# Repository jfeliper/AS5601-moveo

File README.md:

# AS5601-moveo
Placa con AS5601 y optoacopladores para adaptar a 24V
En un conector la salida de los optoacopladores de 24V
En otro conector el bus i2c para configurar el AS5601

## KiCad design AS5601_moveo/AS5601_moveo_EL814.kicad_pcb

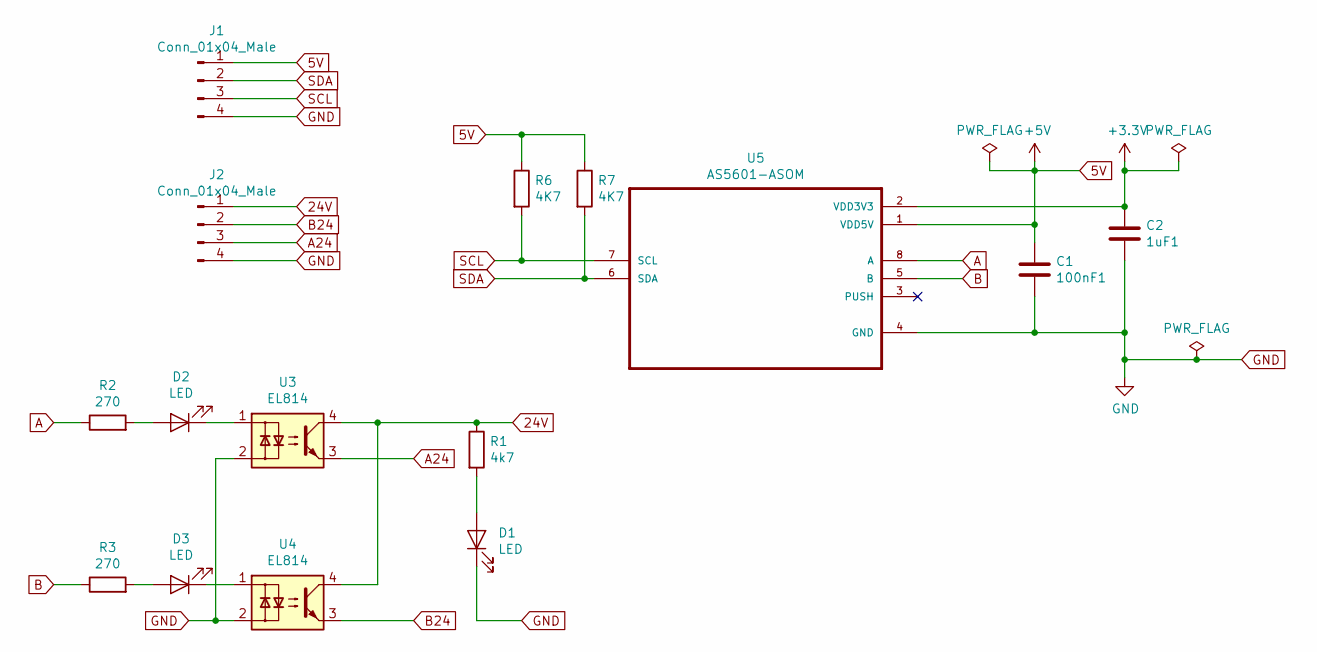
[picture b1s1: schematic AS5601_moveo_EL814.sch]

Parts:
C1: 100nF1; C_1206_3216Metric_Pad1.42x1.75mm_HandSolder
C2: 1uF1; C_1206_3216Metric_Pad1.42x1.75mm_HandSolder
D1, D2, D3: LED; LED_1206_3216Metric_Pad1.42x1.75mm_HandSolder
J1: Conn_01x04_Male; PinSocket_1x04_P2.54mm_Vertical
J2: Conn_01x04_Male; PinHeader_1x04_P2.54mm_Vertical
R1: 4k7; R_1206_3216Metric_Pad1.42x1.75mm_HandSolder
R2, R3: 270; R_1206_3216Metric_Pad1.42x1.75mm_HandSolder
R6, R7: 4K7; R_1206_3216Metric_Pad1.42x1.75mm_HandSolder
U3, U4: EL814; DIP-4_W7.62mm_SMDSocket_SmallPads
U5: AS5601-ASOM; SOIC-8_3.9x4.9mm_P1.27mm

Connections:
5V: C1.1, J1.1, R6.1, R7.1, U5.1 (VDD5V)
24V: J2.1, R1.1, U3.4, U4.4
+3V3: C2.1, U5.2 (VDD3V3)
A: R2.1, U5.8 (A)
A24: J2.3, U3.3
B: R3.1, U5.5 (B)
B24: J2.2, U4.3
GND: C1.2, C2.2, D1.1 (K), J1.4, J2.4, U3.2, U4.2, U5.4 (GND)
unnamed: D1.2 (A), R1.2
unnamed: D2.1 (K), U3.1
unnamed: D2.2 (A), R2.2
unnamed: D3.1 (K), U4.1
unnamed: D3.2 (A), R3.2
SCL: J1.3, R6.2, U5.7 (SCL)
SDA: J1.2, R7.2, U5.6 (SDA)

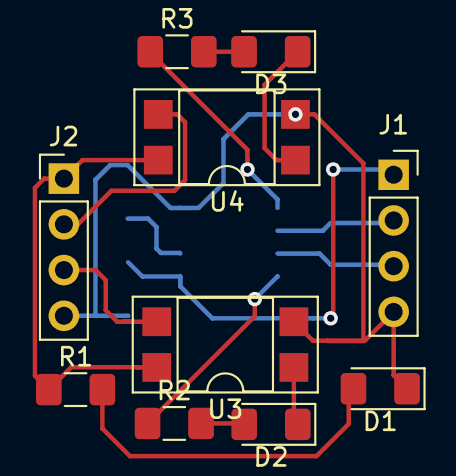
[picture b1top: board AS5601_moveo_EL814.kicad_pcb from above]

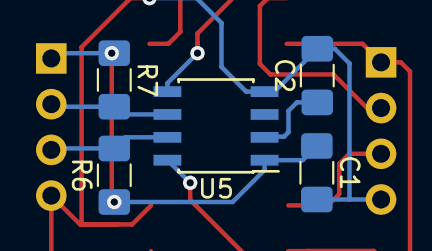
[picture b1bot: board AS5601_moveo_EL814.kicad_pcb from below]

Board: 2 copper layers, 15 parts (5 on the bottom side), 15 nets.

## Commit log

2018-11-26 Add files via upload
    Uso del AS5601 como encoder
    Dos optoacopladores para adaptar los niveles a 24V en un conector
    En otro conector el bus i2c para programar y configurar el AS5601
